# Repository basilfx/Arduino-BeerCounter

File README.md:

# BeerCounter
A beer cork counting system, built around an Arduino, with the love of beer.

## Contents
* Eagle schematic and PCB
* Arduino firmware

## Eagle

### Bill of materials
| Part      | Value         | Device          | Package         |
|-----------|---------------|-----------------|-----------------|
| C1        | 22pF          | C-EU025-024X044 | C025-024X044    |
| C2        | 22pF          | C-EU025-024X044 | C025-024X044    |
| C3        | 100nF         | C-EU025-024X044 | C025-024X044    |
| C4        |               | CPOL-EUTT2D5    | TT2D5           |
| C5        | 100nF         | C-EU025-024X044 | C025-024X044    |
| IC1       | TL072P        | TL072P          | DIL08           |
| IC2       | MEGA8-P       | MEGA8-P         | DIL28-3         |
| ISP       | AVR_SPI_PROG  | AVR_SPI_PROG    | AVR_ICSP        |
| J1        | POWER_JACKSLT | POWER_JACKSLT   | POWER_JACK_SLOT |
| LDR1      |               | M02LOCK         | 1X02_LOCK       |
| LDR2      |               | M02LOCK         | 1X02_LOCK       |
| Q1        | 16MHz         | XTAL/S          | QS              |
| R1        | 4k7           | R-EU_0204/7     | 0204/7          |
| R2        | 1M            | R-EU_0204/7     | 0204/7          |
| R3        | 1M            | R-EU_0204/7     | 0204/7          |
| R4        | 4k7           | TRIM_EU-LI10    | LI10            |
| R5        | 4k7           | TRIM_EU-LI10    | LI10            |
| R6        | 68k           | R-EU_0204/7     | 0204/7          |
| R7        | 68k           | R-EU_0204/7     | 0204/7          |
| R8        | 220           | R-EU_0204/7     | 0204/7          |
| R9        | 220           | R-EU_0204/7     | 0204/7          |
| R10       | 4k7           | R-EU_0204/7     | 0204/7          |
| S1        |               | TAC_SWITCHPTH   | TACTILE-PTH     |
| S2        |               | TAC_SWITCHPTH   | TACTILE-PTH     |

### Board render
Render of the controller board. It measures 2.05x2.30 inch

Render of the display board. It measures 3.70x1.60 inch.

## Arduino
The source can be found under `firmware`. It's build with Arduino 1.6.5, but newer versions should work too.

You need the following libraries:
* [CommandLine](https://github.com/basilfx/Arduino-CommandLine)
* [Timer1](http://playground.arduino.cc/Code/Timer1)

### Firmware
To be done.

### Hardware configuration
For best performance, the light gate should be fitted in a tube, where environment light has little effect.

To calibrate the device, check the [calibration](https://github.com/basilfx/Arduino-BeerCounter/blob/master/docs/Calibration.md) guide.

### Firmware configuration
Once you have the device ready, connect it to the computer via a serial adapter. Hold the setup button, and power cycle the device. The settings for terminal are 115200 baud, 8 bits, no parity and 1 start/stop bit. The terminal has the following commands:

* reset &mdash; Reset the device
* count <value> &mdash; Get/set the initial count
* zeroes <1|0> &mdash; Enable/disable leading zeroes
* restarts &mdash; Get the number of power cycles

## License
See the `LICENSE` file (MIT license).

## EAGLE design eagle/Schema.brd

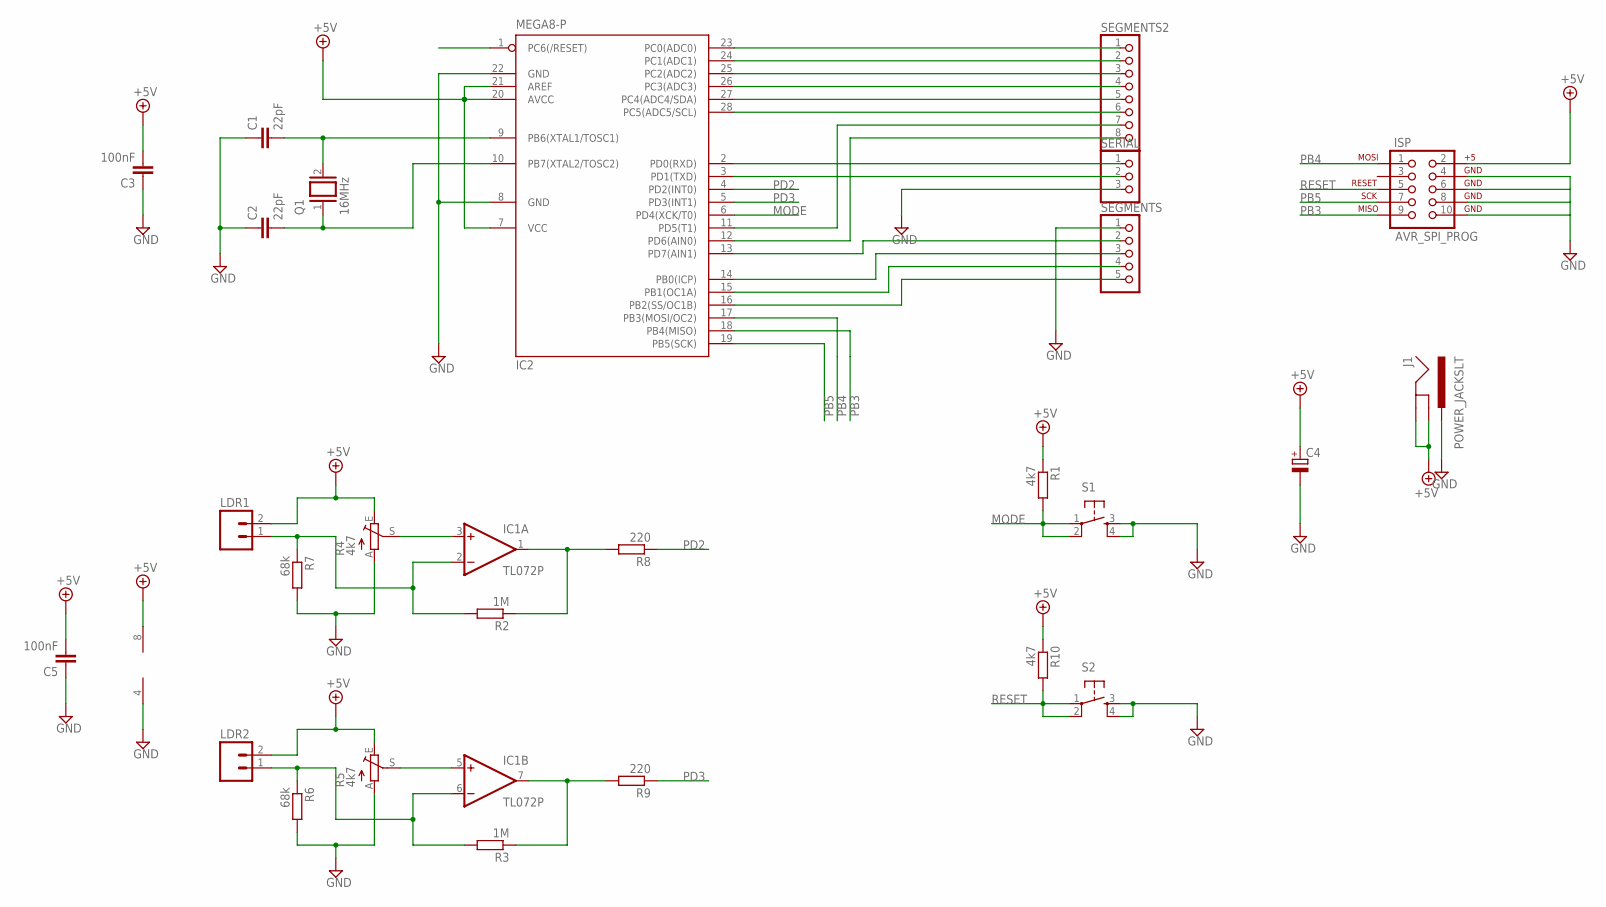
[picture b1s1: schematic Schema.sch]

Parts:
C1, C2: 22pF; C025-024X044
C3, C5: 100nF; C025-024X044
C4: CPOL-EUTT2D5; TT2D5
IC1: TL072P; DIL08
IC2: MEGA8-P; DIL28-3
ISP: AVR_SPI_PROG; AVR_ICSP
J1: POWER_JACKSLT; POWER_JACK_SLOT
LDR1, LDR2: M02LOCK; 1X02_LOCK
Q1: 16MHz; QS
R1, R10: 4k7; 0204/7
R2, R3: 1M; 0204/7
R4, R5: 4k7; LI10
R6, R7: 68k; 0204/7
R8, R9: 220; 0204/7
S1, S2: TAC_SWITCHPTH; TACTILE-PTH
SEGMENTS: PINHD-1X5; 1X05
SEGMENTS2: PINHD-1X8; 1X08
SERIAL: PINHD-1X3; 1X03

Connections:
+5V: C3.2, C4.+, C5.2, IC1.8 (V+), IC2.7 (VCC), IC2.20 (AVCC), IC2.21 (AREF), ISP.2, J1.GND@1 (GNDBREAK), J1.GND@2 (GND), LDR1.2, LDR2.2, R1.1, R4.E, R5.E, R10.1
GND: C1.1, C2.1, C3.1, C4.-, C5.1, IC1.4 (V-), IC2.8 (GND), IC2.22 (GND), ISP.4, ISP.6, ISP.8, ISP.10, J1.PWR, R4.A, R5.A, R6.2, R7.2, S1.3, S1.4, S2.3, S2.4, SEGMENTS.1, SERIAL.3
MODE: IC2.6 (PD4(XCK/T0)), R1.2, S1.1, S1.2
unnamed: C1.2, IC2.9 (PB6(XTAL1/TOSC1)), Q1.2
unnamed: C2.2, IC2.10 (PB7(XTAL2/TOSC2)), Q1.1
unnamed: IC1.1 (OUT), R2.1, R8.2
unnamed: IC2.3 (PD1(TXD)), SERIAL.2
unnamed: IC2.2 (PD0(RXD)), SERIAL.1
unnamed: IC1.7 (OUT), R3.1, R9.2
unnamed: IC1.3 (+IN), R4.S
unnamed: IC1.5 (+IN), R5.S
unnamed: IC1.6 (-IN), LDR2.1, R3.2, R6.1
unnamed: IC1.2 (-IN), LDR1.1, R2.2, R7.1
unnamed: IC2.16 (PB2(SS/OC1B)), SEGMENTS.5
unnamed: IC2.15 (PB1(OC1A)), SEGMENTS.4
unnamed: IC2.14 (PB0(ICP)), SEGMENTS.3
unnamed: IC2.24 (PC1(ADC1)), SEGMENTS2.2
unnamed: IC2.25 (PC2(ADC2)), SEGMENTS2.3
unnamed: IC2.26 (PC3(ADC3)), SEGMENTS2.4
unnamed: IC2.27 (PC4(ADC4/SDA)), SEGMENTS2.5
unnamed: IC2.28 (PC5(ADC5/SCL)), SEGMENTS2.6
unnamed: IC2.12 (PD6(AIN0)), SEGMENTS2.8
unnamed: IC2.11 (PD5(T1)), SEGMENTS2.7
unnamed: IC2.13 (PD7(AIN1)), SEGMENTS.2
PB3: IC2.18 (PB4(MISO)), ISP.9
PB4: IC2.17 (PB3(MOSI/OC2)), ISP.1
PB5: IC2.19 (PB5(SCK)), ISP.7
PD2: IC2.4 (PD2(INT0)), R8.1
PD3: IC2.5 (PD3(INT1)), R9.1
RESET: IC2.1 (PC6(/RESET)), ISP.5, R10.2, S2.1, S2.2
SEGMENTS: IC2.23 (PC0(ADC0)), SEGMENTS2.1

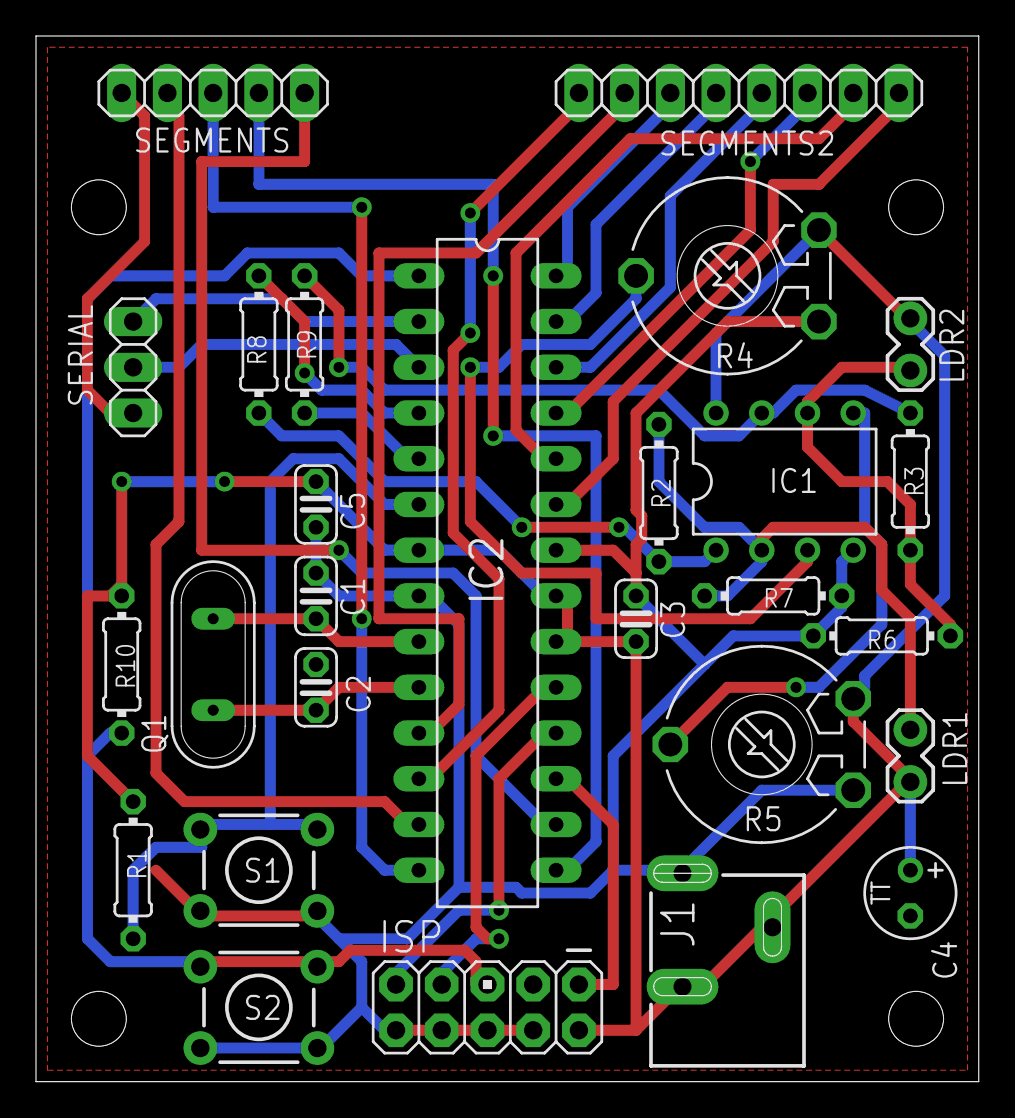
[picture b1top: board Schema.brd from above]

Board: 2 copper layers, 52.4 x 58.1 mm, 31 parts (0 on the bottom side), 31 nets.

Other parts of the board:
U$2, U$3, U$4, U$5: STAND-OFF-TIGHT

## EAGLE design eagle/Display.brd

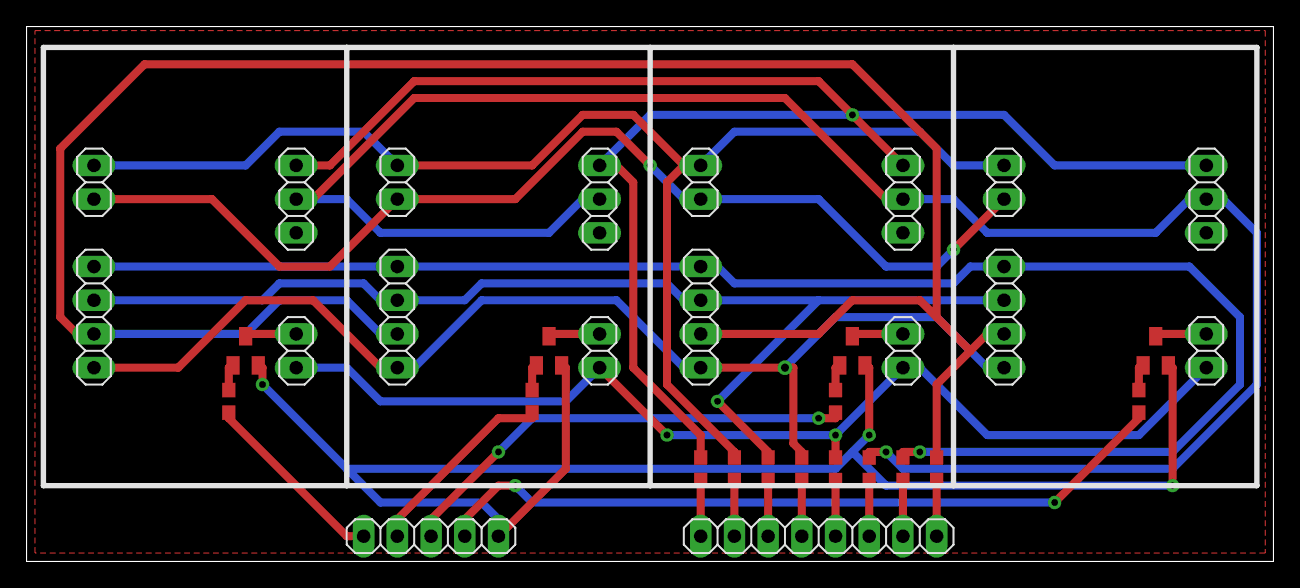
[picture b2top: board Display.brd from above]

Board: 2 copper layers, 94.0 x 40.3 mm, 34 parts (0 on the bottom side), 30 nets.

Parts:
E$1, E$3, E$5, E$7, E$9, E$11, E$13, E$15: 1X02
E$2, E$6, E$10, E$14: 1X03
E$4, E$8, E$12, E$16: 1X04
E$17: 1X08
E$18, E$19, E$20, E$21, E$22, E$23, E$24, E$25, E$26, E$32, E$33, E$34: 0603
E$27, E$28, E$29, E$30: SOT23
E$31: 1X05

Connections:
GND: E$27.2, E$28.2, E$29.2, E$30.2, E$31.5
S$1: E$2.3, E$6.3, E$10.3, E$14.3, E$19.2
S$2: E$3.2, E$7.2, E$11.2, E$15.2, E$20.2
S$3: E$3.1, E$7.1, E$11.1, E$15.1
S$4: E$2.2, E$6.2, E$10.2, E$14.2, E$24.2
S$5: E$4.4, E$8.4, E$12.4, E$16.4, E$25.2
S$6: E$4.3, E$8.3, E$12.3, E$16.3, E$21.2
S$7: E$1.1, E$5.1, E$9.1, E$13.1, E$23.2
S$8: E$4.1, E$8.1, E$12.1, E$16.1, E$22.2
S$9: E$4.2, E$8.2, E$12.2, E$16.2, E$26.2
S$10: E$17.1, E$19.1
S$11: E$17.2, E$20.1
S$12: E$17.3, E$21.1
S$13: E$17.4, E$22.1
S$14: E$17.5, E$23.1
S$15: E$17.6, E$24.1
S$16: E$17.7, E$25.1
S$17: E$17.8, E$26.1
S$18: E$1.2, E$27.3
S$19: E$5.2, E$28.3
S$20: E$9.2, E$29.3
S$21: E$13.2, E$30.3
S$22: E$18.1, E$31.1
S$23: E$18.2, E$27.1
S$24: E$31.2, E$32.2
S$25: E$28.1, E$32.1
S$26: E$29.1, E$33.1
S$27: E$30.1, E$34.2
S$28: E$31.3, E$33.2
S$29: E$31.4, E$34.1

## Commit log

2014-04-15 Updated schematics
2014-04-15 Updated docs
2014-04-15 Added firmware configuration in docs
2014-12-20 Added board render and BOM
2015-08-22 Updated docs with information about calibration.
2015-08-22 Updated code to work with latest CommandLine library.
2015-08-22 Mention the used libraries.

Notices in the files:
parts and their libraries:
SparkFun: Licensing: CC v3.0 Share-Alike You are welcome to use this library for commercial purposes.
